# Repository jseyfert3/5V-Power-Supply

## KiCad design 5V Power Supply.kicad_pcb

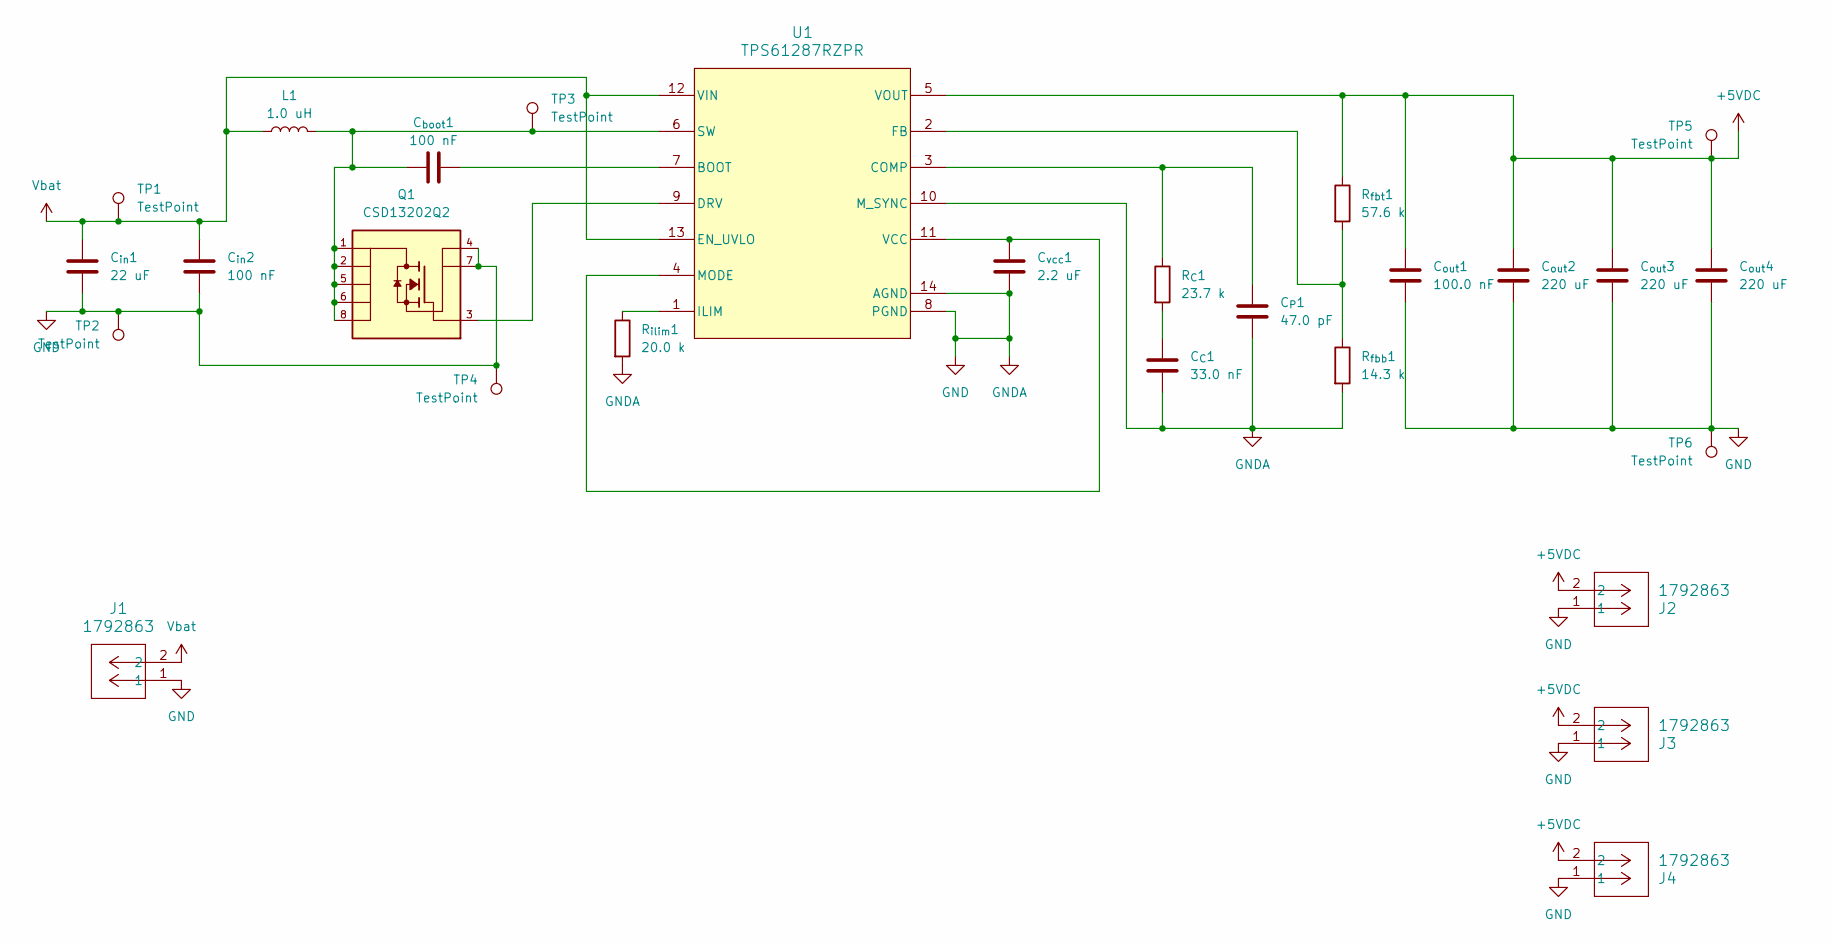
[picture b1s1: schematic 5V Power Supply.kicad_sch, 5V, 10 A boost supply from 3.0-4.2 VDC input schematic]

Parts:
C_{C}1: 33.0 nF; C_0402_1005Metric
C_{P}1: 47.0 pF; C_0805_2012Metric
C_{boot}1: 100 nF; C_0402_1005Metric_Pad0.74x0.62mm_HandSolder
C_{in}1: 22 uF; C_0603_1608Metric
C_{in}2: 100 nF; C_0402_1005Metric_Pad0.74x0.62mm_HandSolder
C_{out}1: 100.0 nF; C_0402_1005Metric_Pad0.74x0.62mm_HandSolder
C_{out}2, C_{out}3, C_{out}4: 220 uF; C_1206_3216Metric_Pad1.33x1.80mm_HandSolder
C_{vcc}1: 2.2 uF; C_0603_1608Metric
J1, J2, J3, J4: 1792863; CONN_1792863_PXC
L1: 1.0 uH; L_Coilcraft_XAL7070-XXX
Q1: CSD13202Q2; TRANS_CSD13202Q2; PARTREV A
R_{C}1: 23.7 k; R_0402_1005Metric
R_{fbb}1: 14.3 k; R_0402_1005Metric_Pad0.72x0.64mm_HandSolder
R_{fbt}1: 57.6 k; R_0402_1005Metric_Pad0.72x0.64mm_HandSolder
R_{ilim}1: 20.0 k; R_0402_1005Metric_Pad0.72x0.64mm_HandSolder
TP1, TP2, TP3, TP4, TP5, TP6: TestPoint; TestPoint_THTPad_D1.0mm_Drill0.5mm
U1: TPS61287RZPR; RZP0014A-MFG

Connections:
+5VDC: C_{out}1.1, C_{out}2.1, C_{out}3.1, C_{out}4.1, J2.2, J3.2, J4.2, R_{fbt}1.1, TP5.1, U1.5 (VOUT)
GND: C_{C}1.2, C_{P}1.2, C_{in}1.2, C_{in}2.2, C_{out}1.2, C_{out}2.2, C_{out}3.2, C_{out}4.2, C_{vcc}1.2, J1.1, J2.1, J3.1, J4.1, Q1.4, Q1.7, R_{fbb}1.2, R_{ilim}1.2, TP2.1, TP4.1, TP6.1, U1.8 (PGND), U1.10 (M_SYNC), U1.14 (AGND)
unnamed: C_{C}1.1, R_{C}1.2
unnamed: C_{boot}1.2, U1.7 (BOOT)
unnamed: C_{P}1.1, R_{C}1.1, U1.3 (COMP)
unnamed: Q1.3, U1.9 (DRV)
unnamed: R_{fbb}1.1, R_{fbt}1.2, U1.2 (FB)
unnamed: R_{ilim}1.1, U1.1 (ILIM)
unnamed: C_{vcc}1.1, U1.4 (MODE), U1.11 (VCC)
unnamed: C_{boot}1.1, L1.2, Q1.1, Q1.2, Q1.5, Q1.6, Q1.8, TP3.1, U1.6 (SW)
Vbat: C_{in}1.1, C_{in}2.1, J1.2, L1.1, TP1.1, U1.12 (VIN), U1.13 (EN_UVLO)

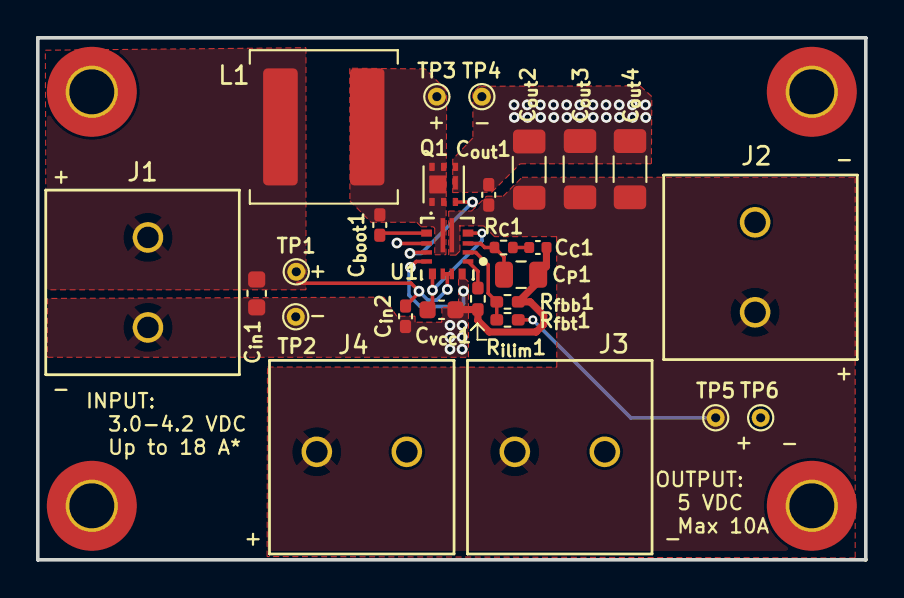
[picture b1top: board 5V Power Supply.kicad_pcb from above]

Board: 2 copper layers, 46.0 x 29.0 mm, 27 parts (0 on the bottom side), 11 nets.

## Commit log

2025-07-10 Initial design, based on TI's WEBENCH tool.
2025-07-14 feat: Mounting holes, power connectors
    Added 2.54 mm ID mounting holes and 4 power connectors. Phoenix Contact spring loaded, good to 16 A, 14-26 AWG wire. 1x on power input from batt, 3x on +5V output.
2025-07-16 Added test points, silkscreening.
    Need to consider input connector. Only rated to 16 A, but at lowest input voltage and highest output current need 18 A on input.
2025-07-17 Updated footprints
    * Some of the footprints didn't match the size of the part picked for this project.
    * Two of the capacitors were swapped.
2025-07-19 feat: Modifications for v1.0
    * Removed vias on input GND
    * Added test points for measuring voltages. Added in pairs, with 2.5 mm spacing for O-scope spring ground probe
    * Removed +5VDC ground pour on bottom layer
    * Replaced the two 0201 components with 0402 components
    * Adjusted some of the copper pour areas
    * Adjusted/added silkscreening

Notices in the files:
5V Power Supply.kicad_pcb:
Released under a GPL-3.0-or-layer license
Copyright 2025 Jonathan Seyfert
5V Power Supply.kicad_sch:
Released under GPL-3.0-or-later license
